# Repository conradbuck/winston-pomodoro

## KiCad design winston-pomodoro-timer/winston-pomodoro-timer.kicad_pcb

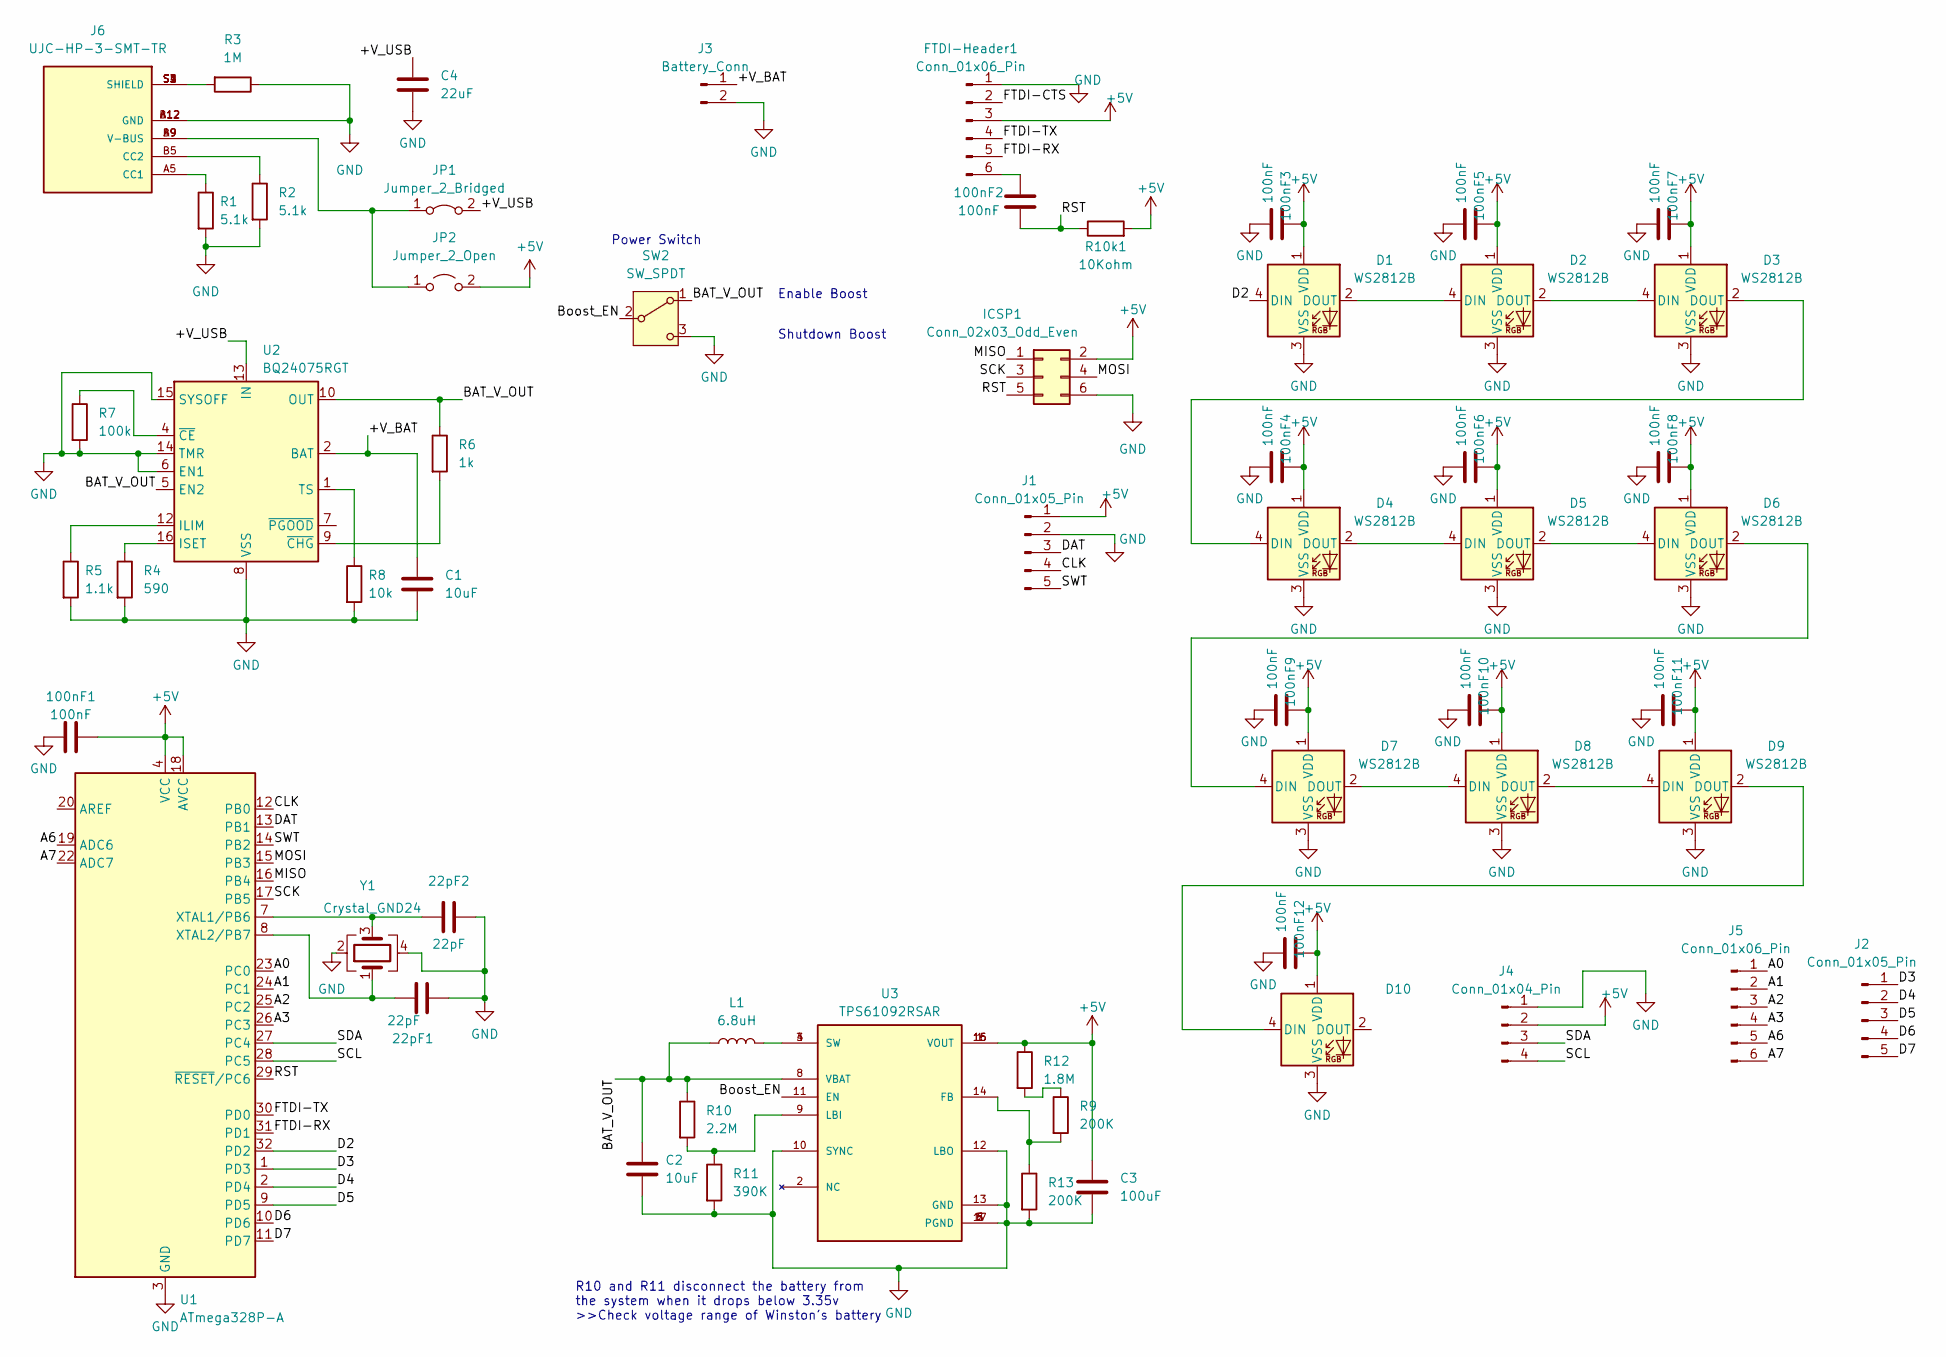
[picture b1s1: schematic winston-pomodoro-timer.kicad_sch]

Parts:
22pF1, 22pF2: 22pF; C_0603_1608Metric; LCSC C376875
100nF1: 100nF; C_0603_1608Metric; LCSC C2830721
100nF2, 100nF3, 100nF4, 100nF5, 100nF6, 100nF7, 100nF8, 100nF9, 100nF10, 100nF11, 100nF12: 100nF; C_0603_1608Metric
C1, C2: 10uF; C_0603_1608Metric
C3: 100uF; C_0805_2012Metric
C4: 22uF; C_0603_1608Metric
D1, D2, D3, D4, D5, D6, D7, D8, D9, D10: WS2812B; LED_WS2812B_PLCC4_5.0x5.0mm_P3.2mm
FTDI-Header1: Conn_01x06_Pin; PinHeader_1x06_P2.54mm_Vertical
ICSP1: Conn_02x03_Odd_Even; PinHeader_2x03_P2.54mm_Vertical
J1, J2: Conn_01x05_Pin; PinHeader_1x05_P2.54mm_Vertical
J3: Battery_Conn; PinSocket_1x02_P2.00mm_Vertical
J4: Conn_01x04_Pin; PinHeader_1x04_P2.54mm_Vertical
J5: Conn_01x06_Pin; PinHeader_1x06_P2.54mm_Vertical
J6: UJC-HP-3-SMT-TR; CUI_UJC-HP-3-SMT-TR; PARTREV 04/30/2020
JP1: Jumper_2_Bridged; SolderJumper-2_P1.3mm_Bridged2Bar_RoundedPad1.0x1.5mm
JP2: Jumper_2_Open; SolderJumper-2_P1.3mm_Open_RoundedPad1.0x1.5mm
L1: 6.8uH; L_Bourns-SRN4018
R1, R2: 5.1k; R_0603_1608Metric
R3: 1M; R_0603_1608Metric
R4: 590; R_0603_1608Metric
R5: 1.1k; R_0603_1608Metric
R6: 1k; R_0603_1608Metric
R7: 100k; R_0603_1608Metric
R8: 10k; R_0603_1608Metric
R9, R13: 200K; R_0603_1608Metric
R10: 2.2M; R_0603_1608Metric
R10k1: 10Kohm; C_0805_2012Metric_Pad1.18x1.45mm_HandSolder
R11: 390K; R_0603_1608Metric
R12: 1.8M; C_0603_1608Metric
SW2: SW_SPDT; SW_Slide_1P2T_CK_OS102011MS2Q
U1: ATmega328P-A; TQFP-32_7x7mm_P0.8mm; LCSC C132230
U2: BQ24075RGT; VQFN-16-1EP_3x3mm_P0.5mm_EP1.6x1.6mm
U3: TPS61092RSAR; CONV_TPS61092RSAR; PARTREV C
Y1: Crystal_GND24; Crystal_SMD_3225-4Pin_3.2x2.5mm_HandSoldering; LCSC C1985977

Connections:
+5V: 100nF1.1, 100nF3.2, 100nF4.2, 100nF5.2, 100nF6.2, 100nF7.2, 100nF8.2, 100nF9.2, 100nF10.2, 100nF11.2, 100nF12.2, C3.1, D1.1 (VDD), D2.1 (VDD), D3.1 (VDD), D4.1 (VDD), D5.1 (VDD), D6.1 (VDD), D7.1 (VDD), D8.1 (VDD), D9.1 (VDD), D10.1 (VDD), FTDI-Header1.3, ICSP1.2, J1.1, J4.2, JP2.2 (B), R10k1.2, R12.1, U1.4 (VCC), U1.6 (VCC), U1.18 (AVCC), U3.1 (VOUT), U3.15 (VOUT), U3.16 (VOUT)
/+V_BAT: C1.1, J3.1, U2.2 (BAT), U2.3 (BAT)
/+V_USB: C4.1, JP1.2 (B), U2.13 (IN)
/A0: J5.1, U1.23 (PC0)
/A1: J5.2, U1.24 (PC1)
/A2: J5.3, U1.25 (PC2)
/A3: J5.4, U1.26 (PC3)
/A6: J5.5, U1.19 (ADC6)
/A7: J5.6, U1.22 (ADC7)
/BAT_V_OUT: C2.1, L1.1, R6.1, R10.1, SW2.1 (A), U2.5 (EN2), U2.10 (OUT), U2.11 (OUT), U3.8 (VBAT)
/Boost_EN: SW2.2 (B), U3.11 (EN)
/CLK: J1.4, U1.12 (PB0)
/D2: D1.4 (DIN), U1.32 (PD2)
/D3: J2.1, U1.1 (PD3)
/D4: J2.2, U1.2 (PD4)
/D5: J2.3, U1.9 (PD5)
/D6: J2.4, U1.10 (PD6)
/D7: J2.5, U1.11 (PD7)
/DAT: J1.3, U1.13 (PB1)
/FTDI-CTS: FTDI-Header1.2
/FTDI-RX: FTDI-Header1.5, U1.31 (PD1)
/FTDI-TX: FTDI-Header1.4, U1.30 (PD0)
/MISO: ICSP1.1, U1.16 (PB4)
/MOSI: ICSP1.4, U1.15 (PB3)
/RST: 100nF2.1, ICSP1.5, R10k1.1, U1.29 (~RESET/PC6)
/SCK: ICSP1.3, U1.17 (PB5)
/SCL: J4.4, U1.28 (PC5)
/SDA: J4.3, U1.27 (PC4)
/SWT: J1.5, U1.14 (PB2)
GND: 22pF1.1, 22pF2.2, 100nF1.2, 100nF3.1, 100nF4.1, 100nF5.1, 100nF6.1, 100nF7.1, 100nF8.1, 100nF9.1, 100nF10.1, 100nF11.1, 100nF12.1, C1.2, C2.2, C3.2, C4.2, D1.3 (VSS), D2.3 (VSS), D3.3 (VSS), D4.3 (VSS), D5.3 (VSS), D6.3 (VSS), D7.3 (VSS), D8.3 (VSS), D9.3 (VSS), D10.3 (VSS), FTDI-Header1.1, ICSP1.6, J1.2, J3.2, J4.1, J6.A12 (GND), J6.B12 (GND), R1.2, R2.2, R3.1, R4.2, R5.2, R7.2, R8.2, R11.2, R13.2, SW2.3 (C), U1.3 (GND), U1.5 (GND), U1.21 (GND), U2.6 (EN1), U2.8 (VSS), U2.14 (TMR), U2.15 (SYSOFF), U2.17 (VSS), U3.5 (PGND), U3.6 (PGND), U3.7 (PGND), U3.10 (SYNC), U3.12 (LBO), U3.13 (GND), U3.17 (PGND), U3.18, U3.19, U3.20, U3.21, U3.22, U3.23, U3.24, U3.25, U3.26, Y1.2, Y1.4
unnamed: D1.2 (DOUT), D2.4 (DIN)
unnamed: D2.2 (DOUT), D3.4 (DIN)
unnamed: D3.2 (DOUT), D4.4 (DIN)
unnamed: D4.2 (DOUT), D5.4 (DIN)
unnamed: D5.2 (DOUT), D6.4 (DIN)
unnamed: D6.2 (DOUT), D7.4 (DIN)
unnamed: D7.2 (DOUT), D8.4 (DIN)
unnamed: D8.2 (DOUT), D9.4 (DIN)
unnamed: D9.2 (DOUT), D10.4 (DIN)
unnamed: 100nF2.2, FTDI-Header1.6
unnamed: J6.A5 (CC1), R1.1
unnamed: J6.B5 (CC2), R2.1
unnamed: J6.S1 (SHIELD), J6.S2 (SHIELD), J6.S3 (SHIELD), J6.S4 (SHIELD), R3.2
unnamed: J6.A9 (V-BUS), J6.B9 (V-BUS), JP1.1 (A), JP2.1 (A)
unnamed: L1.2, U3.3 (SW), U3.4 (SW)
unnamed: R9.1, R12.2
unnamed: 22pF2.1, U1.7 (XTAL1/PB6), Y1.3
unnamed: 22pF1.2, U1.8 (XTAL2/PB7), Y1.1
unnamed: R5.1, U2.12 (ILIM)
unnamed: R4.1, U2.16 (ISET)
unnamed: R8.1, U2.1 (TS)
unnamed: R7.1, U2.4 (~CE)
unnamed: R6.2, U2.9 (~CHG)
unnamed: R9.2, R13.1, U3.14 (FB)
unnamed: R10.2, R11.1, U3.9 (LBI)

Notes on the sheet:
Enable Boost
R10 and R11 disconnect the battery from the system when it drops below 3.35v >>Check voltage range of Winston's battery
Shutdown Boost
Power Switch

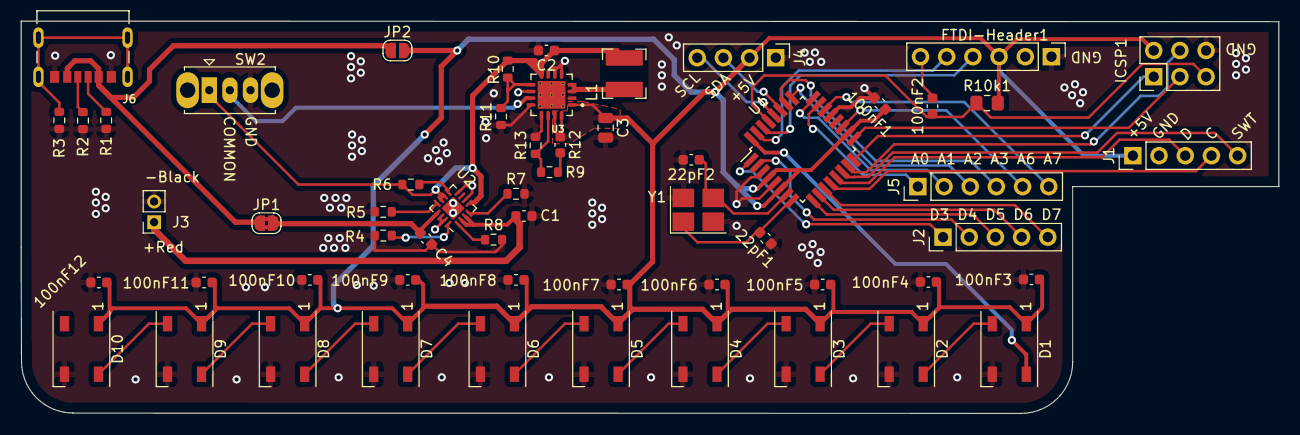
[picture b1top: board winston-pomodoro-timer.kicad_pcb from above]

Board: 2 copper layers, 122.0 x 38.0 mm, 58 parts (0 on the bottom side), 54 nets.

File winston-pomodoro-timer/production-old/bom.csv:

Designator,Footprint,Quantity,Value,LCSC Part #
100NF1,0603,1,100nF,C2830721
"100NF10, 100NF11, 100NF12, 100NF2, 100NF3, 100NF4, 100NF5, 100NF6, 100NF7, 100NF8, 100NF9",0603,11,100nF,C88219,
"22PF1, 22PF2",0603,2,22pF,C376875
"C1, C2",0603,2,10uF,
C3,0805,1,100uF,
C4,0603,1,22uF,
"D1, D10, D2, D3, D4, D5, D6, D7, D8, D9",LED_WS2812B_PLCC4_5.0x5.0mm_P3.2mm,10,WS2812B,
"FTDI-HEADER1, J5",PinHeader_1x06_P2.54mm_Vertical,2,Conn_01x06_Pin,
ICSP1,PinHeader_2x03_P2.54mm_Vertical,1,Conn_02x03_Odd_Even,
"J1, J2",PinHeader_1x05_P2.54mm_Vertical,2,Conn_01x05_Pin,
J3,PinSocket_1x02_P2.00mm_Vertical,1,Battery_Conn,C5175230,
J4,PinHeader_1x04_P2.54mm_Vertical,1,Conn_01x04_Pin,
J6,CUI_UJC-HP-3-SMT-TR,1,UJC-HP-3-SMT-TR,C7507406,
JP1,SolderJumper-2_P1.3mm_Bridged2Bar_RoundedPad1.0x1.5mm,1,Jumper_2_Bridged,
JP2,SolderJumper-2_P1.3mm_Open_RoundedPad1.0x1.5mm,1,Jumper_2_Open,
L1,L_Bourns-SRN4018,1,6.8uH,
"R1, R2",0603,2,5.1k,
R10,0603,1,2.2M,
R10K1,0805,1,10Kohm,
R11,0603,1,390K,
R12,0603,1,1.8M,
"R13, R9",0603,2,200K,
R3,0603,1,1M,
R4,0603,1,590,
R5,0603,1,1.1k,
R6,0603,1,1k,
R7,0603,1,100k,
R8,0603,1,10k,
SW2,SW_Slide_1P2T_CK_OS102011MS2Q,1,SW_SPDT,
U1,TQFP-32_7x7mm_P0.8mm,1,ATmega328P-A,C132230
U2,VQFN-16-1EP_3x3mm_P0.5mm_EP1.6x1.6mm,1,BQ24075RGT,
U3,CONV_TPS61092RSAR,1,TPS61092RSAR,
Y1,Crystal_SMD_3225-4Pin_3.2x2.5mm_HandSoldering,1,Crystal_GND24,C70562,

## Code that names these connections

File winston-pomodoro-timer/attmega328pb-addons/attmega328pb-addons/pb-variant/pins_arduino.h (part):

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#define digitalPinToPCMSKbit(p)  (((p) <= 7) ? (p) : (((p) <= 13) ? ((p) - 8) : ((p) <= 21) ? ((p) - 14) : ((p) == 22) ? ((p) - 16) : ((p) - 23)))
#endif

#define PIN_PD0 0
#define PIN_PD1 1
#define PIN_PD2 2
#define PIN_PD3 3
#define PIN_PD4 4
#define PIN_PD5 5
#define PIN_PD6 6
#define PIN_PD7 7
#define PIN_PB0 8
#define PIN_PB1 9
#define PIN_PB2 10
#define PIN_PB3 11
#define PIN_PB4 12
#define PIN_PB5 13
#define PIN_PC0 14 // A0
#define PIN_PC1 15 // A1
#define PIN_PC2 16 // A2
#define PIN_PC3 17 // A3
#define PIN_PC4 18 // A4
#define PIN_PC5 19 // A5
#define PIN_PB6 20 // XTAL1
#define PIN_PB7 21 // XTAL2
#define PIN_PC6 22 // RESET
#define PIN_PE0 23
#define PIN_PE1 24
#define PIN_PE2 25 // A6
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};

const uint8_t PROGMEM digital_pin_to_port_PGM[] = {
	PD, // PD0 - D0
	PD, // PD1 - D1
	PD, // PD2 - D2
	PD, // PD3 - D3
	PD, // PD4 - D4
	PD, // PD5 - D5
	PD, // PD6 - D6
	PD, // PD7 - D7
	PB, // PB0 - D8
	PB, // PB1 - D9
	PB, // PB2 - D10
	PB, // PB3 - D11
	PB, // PB4 - D12
	PB, // PB5 - D13
	PC, // PC0 - D14 / A0
	PC, // PC1 - D15 / A1
	PC, // PC2 - D16 / A2
	PC, // PC3 - D17 / A3
	PC, // PC4 - D18 / A4
	PC, // PC5 - D19 / A5
	PB, // PB6 - D20 / XTAL1
	PB, // PB7 - D21 / XTAL2
	PC, // PC6 - D22 / RESET
	PE, // PE0 - D23
	PE, // PE1 - D24
	PE, // PE2 - D25 / A6
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};

const uint8_t PROGMEM digital_pin_to_bit_mask_PGM[] = {
	_BV(0), // PD0 - D0
	_BV(1), // PD1 - D1
	_BV(2), // PD2 - D2
	_BV(3), // PD3 - D3
	_BV(4), // PD4 - D4
	_BV(5), // PD5 - D5
	_BV(6), // PD6 - D6
	_BV(7), // PD7 - D7
	_BV(0), // PB0 - D8
	_BV(1), // PB1 - D9
	_BV(2), // PB2 - D10
	_BV(3), // PB3 - D11
	_BV(4), // PB4 - D12
	_BV(5), // PB5 - D13
	_BV(0), // PC0 - D14 / A0
	_BV(1), // PC1 - D15 / A1
	_BV(2), // PC2 - D16 / A2
	_BV(3), // PC3 - D17 / A3
	_BV(4), // PC4 - D18 / A4
	_BV(5), // PC5 - D19 / A5
	_BV(6), // PB6 - D20 / XTAL1
	_BV(7), // PB7 - D21 / XTAL2
	_BV(6), // PC6 - D22 / RESET
	_BV(0), // PE0 - D23
	_BV(1), // PE1 - D24
	_BV(2), // PE2 - D25 / A6
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
const uint8_t PROGMEM digital_pin_to_timer_PGM[] = {
#if defined(__AVR_ATmega48PB__) || defined(__AVR_ATmega88PB__) || defined(__AVR_ATmega168PB__)
	NOT_ON_TIMER, // PD0 - D0
	NOT_ON_TIMER, // PD1 - D1
	NOT_ON_TIMER, // PD2 - D2
#elif	defined(__AVR_ATmega328PB__)
  TIMER3A,      // PD0 - D0
	TIMER4A,      // PD1 - D1
	TIMER4B,      // PD2 - D2 -> TIMER3B is also an option
#endif
	TIMER2B,      // PD3 - D3
	NOT_ON_TIMER, // PD4 - D4
	TIMER0B,      // PD5 - D5
	TIMER0A,      // PD6 - D6
	NOT_ON_TIMER, // PD7 - D7
	NOT_ON_TIMER, // PB0 - D8
	TIMER1A,      // PB1 - D9
	TIMER1B,      // PB2 - D10
	TIMER2A,      // PB3 - D11
	NOT_ON_TIMER, // PB4 - D12
	NOT_ON_TIMER, // PB5 - D13
	NOT_ON_TIMER, // PC0 - D14 / A0
	NOT_ON_TIMER, // PC1 - D15 / A1
	NOT_ON_TIMER, // PC2 - D16 / A2
	NOT_ON_TIMER, // PC3 - D17 / A3
	NOT_ON_TIMER, // PC4 - D18 / A4
	NOT_ON_TIMER, // PC5 - D19 / A5
	NOT_ON_TIMER, // PB6 - D20 / XTAL1
	NOT_ON_TIMER, // PB7 - D21 / XTAL2
	NOT_ON_TIMER, // PC6 - D22 / RESET
	NOT_ON_TIMER, // PE0 - D23
	NOT_ON_TIMER, // PE1 - D24
	NOT_ON_TIMER, // PE2 - D25 / A6
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
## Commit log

2024-10-30 adding pcb to repo
2024-10-30 added special-parts.txt
2024-11-01 added usbc port and started battery controller
2024-11-02 finished layout and routing
2024-11-03 added battery override jumpers
2024-11-03 added rounded corners
2024-11-03 added manufacturing files
2024-11-07 added kevins design feedback notes to special-parts
2024-11-07 added 3d model of pcb
2024-11-10 added rev2 pcb
2024-11-11 added pictures of pcb for documentation
2024-11-15 added firmware
2024-11-17 added updated firmware and board config
2024-11-17 added board config
2024-11-17 added rev2
2024-11-17 added stuff
2024-11-17 added rotary good algo
2024-11-17 added rev1 firmware
2024-11-17 added pin declarations
2024-11-17 wrapped up v1
2024-11-23 case 6 nor 7 running despite CONSTANT state value in switch statement
2024-11-23 code works fuly
2024-11-23 added timing adjustments
2024-12-01 updated length of second in firmware-timer-if-chain <<< PROPER CODE
2024-12-01 added flowchart and task organization
2024-12-08 eploading recent code

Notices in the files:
winston-pomodoro-timer/attmega328pb-addons/attmega328pb-addons/pb-variant/pins_arduino.h:
Copyright (c) 2007 David A. Mellis
Public License along with this library; if not, write to the
Free Software Foundation, Inc., 59 Temple Place, Suite 330,
Boston, MA  02111-1307  USA
